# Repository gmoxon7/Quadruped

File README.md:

# Nano switch
A repository containing a back up of all required files for the production of the Nano switch (custom low profile limit switch)

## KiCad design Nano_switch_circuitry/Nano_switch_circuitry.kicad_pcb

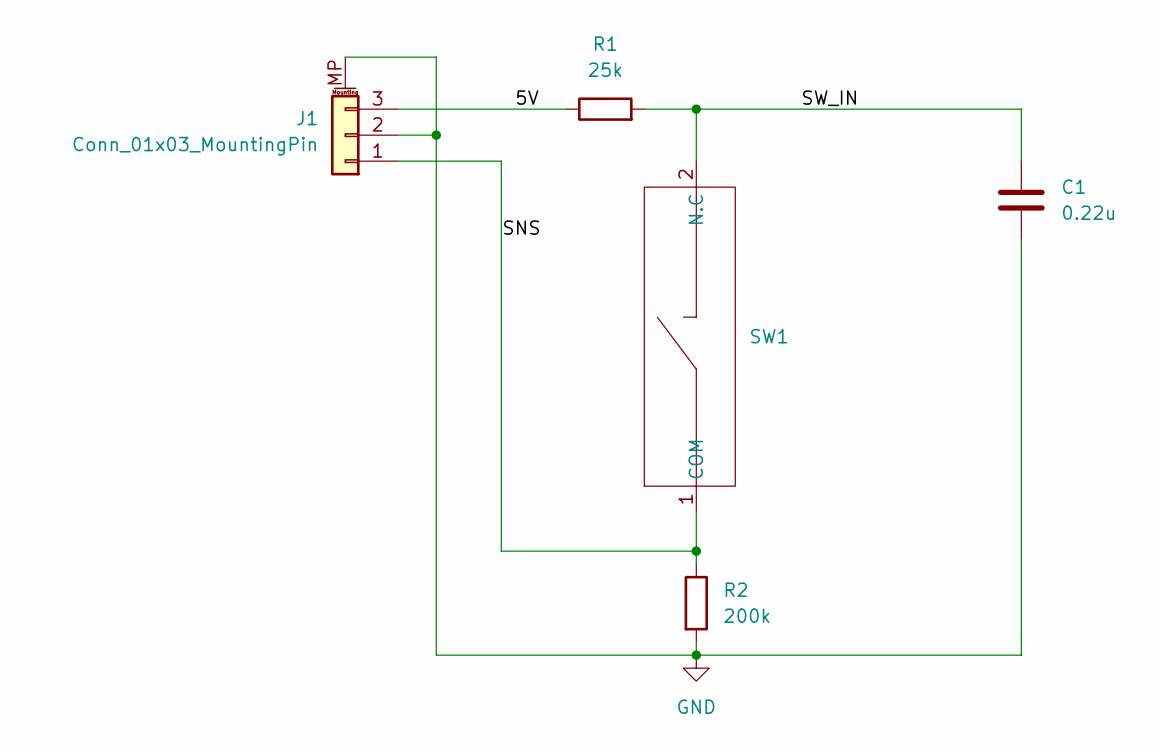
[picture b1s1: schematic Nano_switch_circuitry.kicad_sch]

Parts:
C1: 0.22u; R_0402_1005Metric
J1: Conn_01x03_MountingPin; JST_SH_SM03B-SRSS-TB_1x03-1MP_P1.00mm_Horizontal
R1: 25k; R_0402_1005Metric
R2: 200k; R_0402_1005Metric
SW1: D3SH-B1R1

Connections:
/5V: J1.3, R1.1
/SNS: J1.1, R2.1, SW1.1 (COM)
/SW_IN: C1.1, R1.2, SW1.2 (N.C)
GND: C1.2, J1.2, J1.MP (MountPin), R2.2

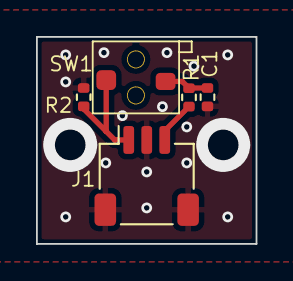
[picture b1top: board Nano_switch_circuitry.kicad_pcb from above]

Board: 2 copper layers, 12.2 x 11.5 mm, 5 parts (0 on the bottom side), 4 nets.

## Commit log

2024-05-06 The gerbers for the Nano switch design.
2024-07-23 Add files via upload
    Added all files related to the design and manufacture of version V1.0 of the nanoswitch circuitry
